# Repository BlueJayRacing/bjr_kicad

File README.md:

# bjr_kicad
jhu blue jay racing daq kicad pcb files

Note: 20xt is mainly for legacy

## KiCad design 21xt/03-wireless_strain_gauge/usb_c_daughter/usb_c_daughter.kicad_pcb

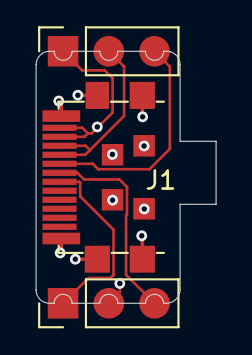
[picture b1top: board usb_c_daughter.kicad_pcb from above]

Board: 4 copper layers, 10.0 x 14.0 mm, 3 parts (0 on the bottom side), 6 nets.

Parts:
J1: USB_C_Plug_USB2.0; USB_C_MOUNT
J3: Conn_01x03; PinHeader_1x03_P2.54mm_Vertical
Je: Conn_01x03; PinSocket_1x03_P2.54mm_Vertical

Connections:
CC: J1.A5 (CC), Je.3
D+: J1.A6 (D+), J3.3
D-: J1.A7 (D-), J3.1
GND: J1.A1 (GND), J1.B12 (GND), Je.1
SHIELD: J1.S1 (SHIELD), J3.2
VBUS: J1.A4 (VBUS), J1.B9 (VBUS), Je.2

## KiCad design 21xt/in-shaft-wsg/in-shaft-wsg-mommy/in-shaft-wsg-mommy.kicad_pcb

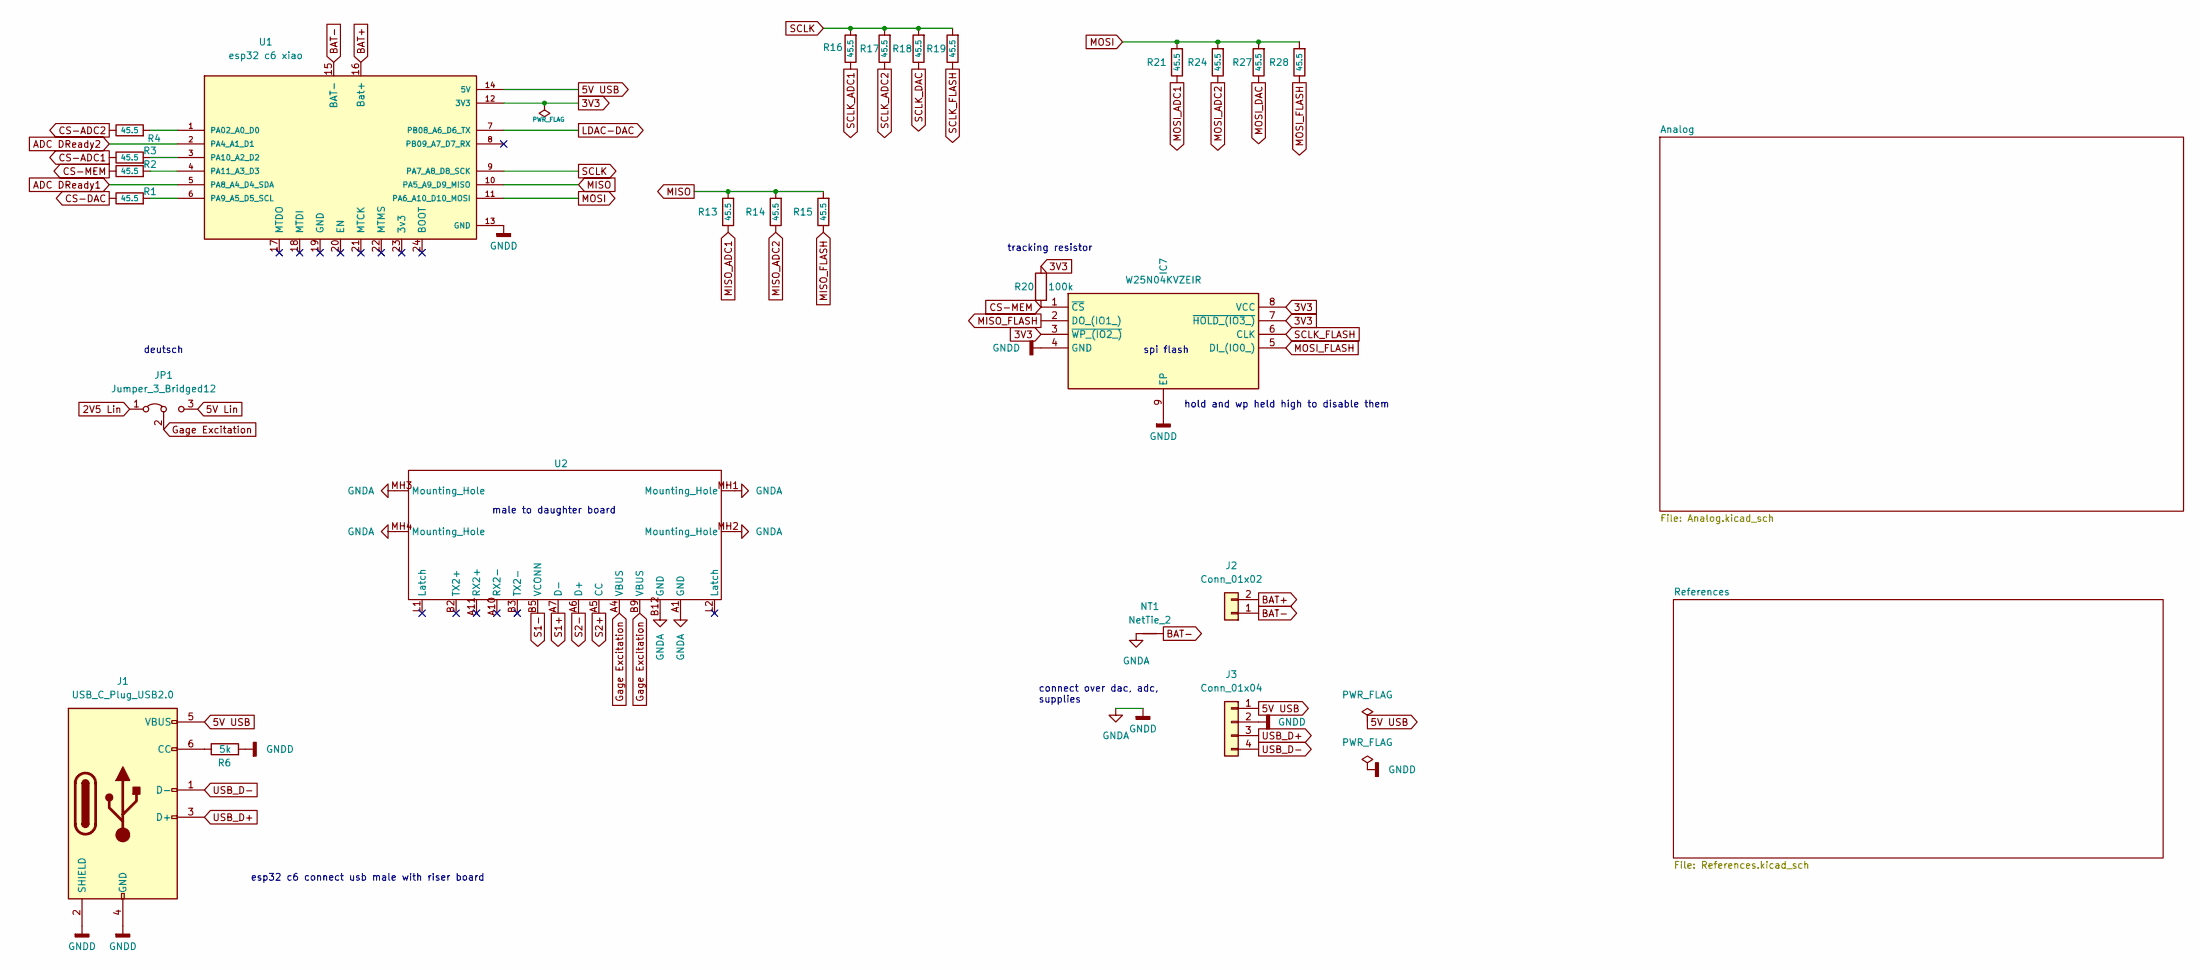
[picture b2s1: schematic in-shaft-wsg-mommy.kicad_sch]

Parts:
IC7: W25N04KVZEIR; SON127P800X600X80-9N-D; Mouser Part Number 454-W25N04KVZEIR
J1: USB_C_Plug_USB2.0; USB_C_PLACE
J2: Conn_01x02; JST_PH_S2B-PH-K_1x02_P2.00mm_Horizontal
J3: Conn_01x04; PinHeader_1x04_P2.00mm_Vertical
JP1: Jumper_3_Bridged12; SolderJumper-3_P2.0mm_Open_TrianglePad1.0x1.5mm
NT1: NetTie_2; NetTie-2_SMD_Pad0.5mm
R1, R2, R3, R4, R13, R14, R15, R16, R17, R18, R19, R21, R24, R27, R28: 45.5; R_0402_1005Metric
R6: 5k; R_0402_1005Metric
R20: 100k; R_0402_1005Metric
U1: esp32 c6 xiao; esp32 c6 smt; PARTREV N/A
U2: USB_C_MOUNT

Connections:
2V5 Lin: JP1.1 (A); also elsewhere on the board
3V3: IC7.3 (~WP_(IO2_)), IC7.7 (~HOLD_(IO3_)), IC7.8 (VCC), R20.1, U1.12 (3V3); also elsewhere on the board
5V Lin: JP1.3 (B); also elsewhere on the board
5V USB: J1.5 (VBUS), J3.1, U1.14 (5V)
ADC DReady1: U1.5 (PA8_A4_D4_SDA); also elsewhere on the board
ADC DReady2: U1.2 (PA4_A1_D1); also elsewhere on the board
BAT+: J2.2, U1.16 (Bat+)
BAT-: J2.1, NT1.2, U1.15 (BAT-)
CS-ADC1: R3.1; also elsewhere on the board
CS-ADC2: R4.1; also elsewhere on the board
CS-DAC: R1.1; also elsewhere on the board
CS-MEM: IC7.1 (~CS), R2.1, R20.2
GNDA: IC7.4 (GND), IC7.9 (EP), J1.2 (SHIELD), J1.4 (GND), J3.2, NT1.1, R6.2, U1.13 (GND), U2.A1 (GND), U2.B12 (GND), U2.MH1 (Mounting_Hole), U2.MH2 (Mounting_Hole), U2.MH3 (Mounting_Hole), U2.MH4 (Mounting_Hole); also elsewhere on the board
Gage Excitation: JP1.2 (C), U2.A4 (VBUS), U2.B9 (VBUS); also elsewhere on the board
LDAC-DAC: U1.7 (PB08_A6_D6_TX); also elsewhere on the board
MISO: R13.2, R14.2, R15.2, U1.10 (PA5_A9_D9_MISO)
MISO_ADC1: R13.1; also elsewhere on the board
MISO_ADC2: R14.1; also elsewhere on the board
MISO_FLASH: IC7.2 (DO_(IO1_)), R15.1
MOSI: R21.2, R24.2, R27.2, R28.2, U1.11 (PA6_A10_D10_MOSI)
MOSI_ADC1: R21.1; also elsewhere on the board
MOSI_ADC2: R24.1; also elsewhere on the board
MOSI_DAC: R27.1; also elsewhere on the board
MOSI_FLASH: IC7.5 (DI_(IO0_)), R28.1
unnamed: J1.6 (CC), R6.1
unnamed: R4.2, U1.1 (PA02_A0_D0)
unnamed: R1.2, U1.6 (PA9_A5_D5_SCL)
unnamed: R3.2, U1.3 (PA10_A2_D2)
unnamed: R2.2, U1.4 (PA11_A3_D3)
S1+: U2.A7 (D-); also elsewhere on the board
S1-: U2.B5 (VCONN); also elsewhere on the board
S2+: U2.A5 (CC); also elsewhere on the board
S2-: U2.A6 (D+); also elsewhere on the board
SCLK: R16.2, R17.2, R18.2, R19.2, U1.9 (PA7_A8_D8_SCK)
SCLK_ADC1: R16.1; also elsewhere on the board
SCLK_ADC2: R17.1; also elsewhere on the board
SCLK_DAC: R18.1; also elsewhere on the board
SCLK_FLASH: IC7.6 (CLK), R19.1
USB_D+: J1.3 (D+), J3.3
USB_D-: J1.1 (D-), J3.4

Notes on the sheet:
connect over dac, adc, supplies
esp32 c6 connect usb male with riser board
spi flash
male to daughter board
deutsch
hold and wp held high to disable them
tracking resistor

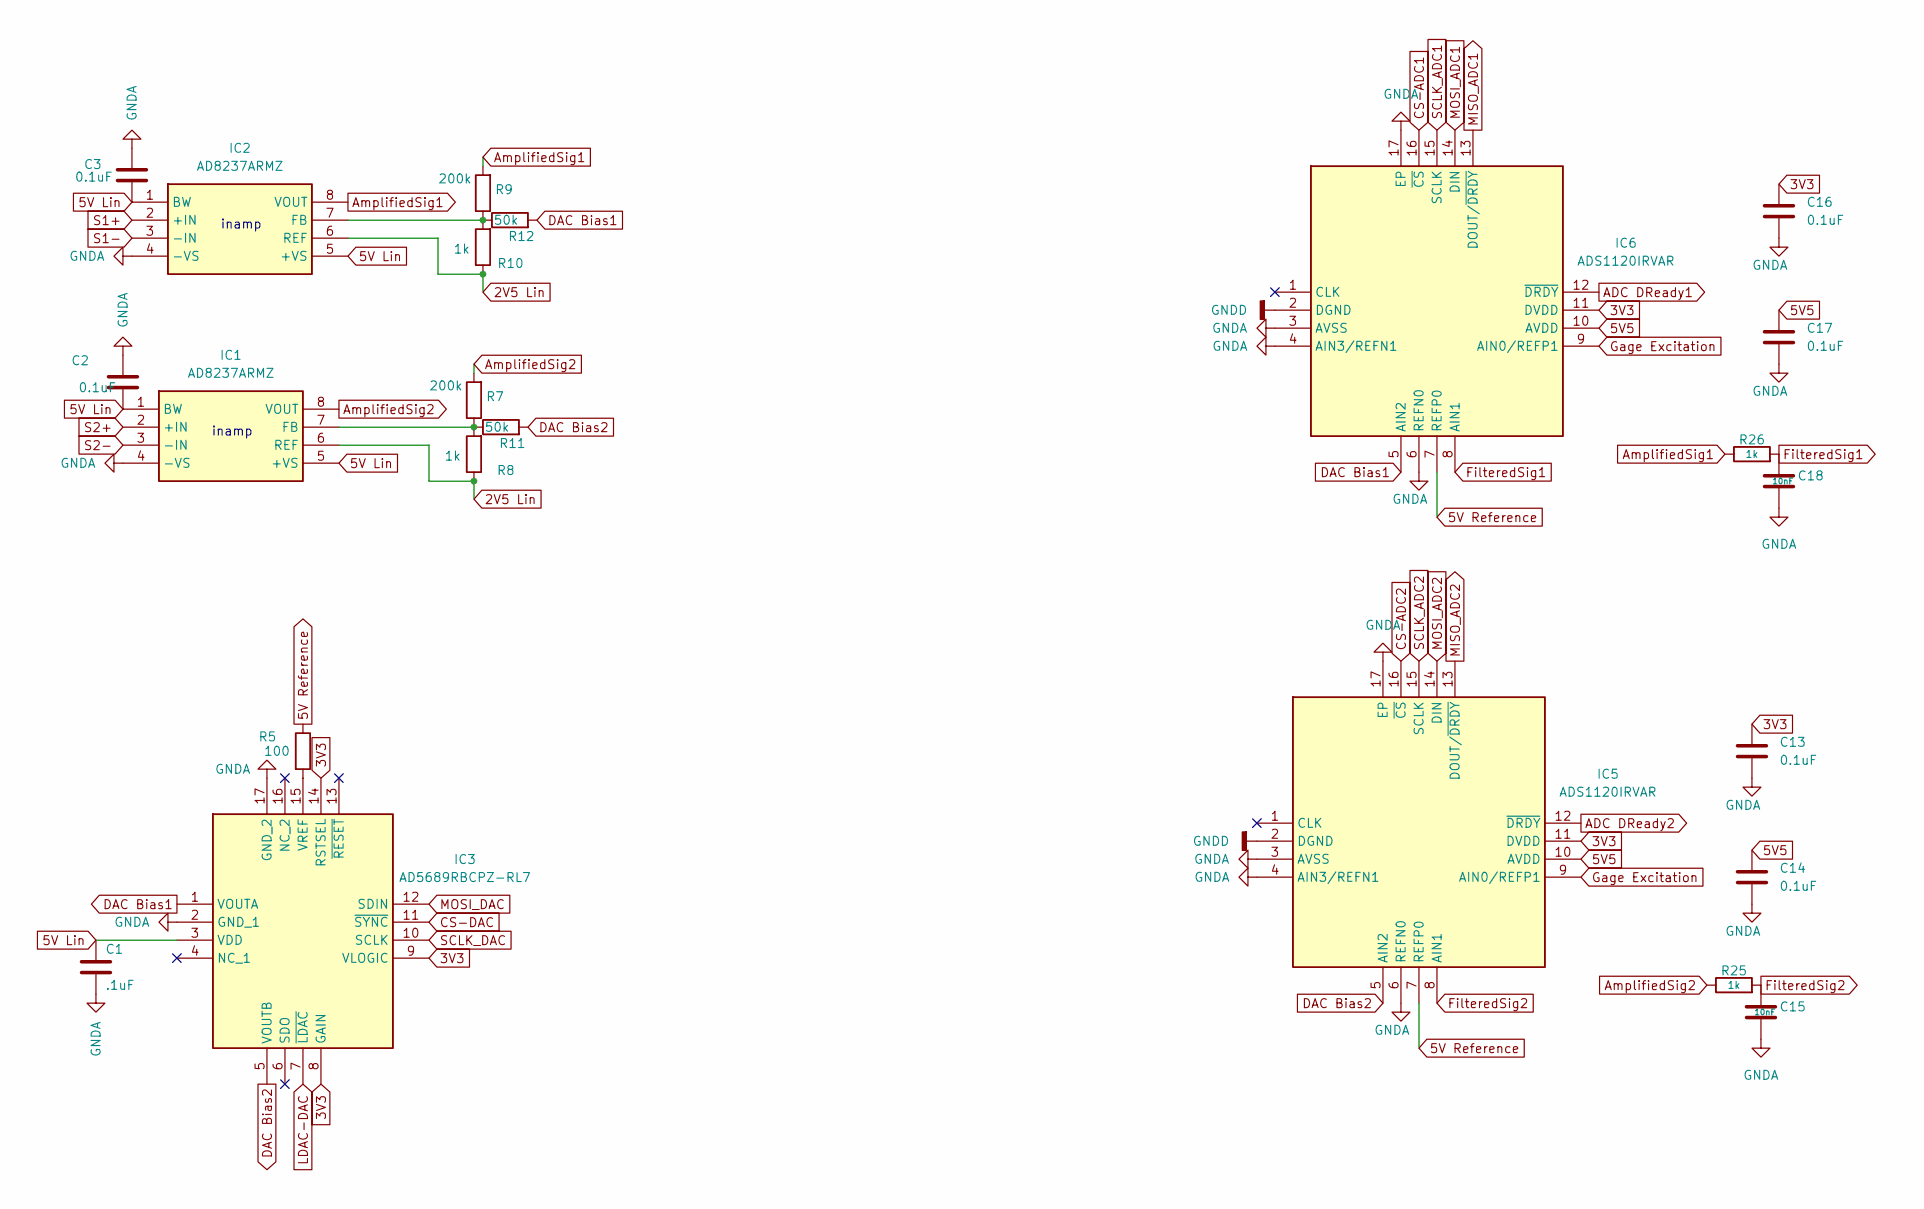
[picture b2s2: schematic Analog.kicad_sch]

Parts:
C1: .1uF; C_0402_1005Metric
C2, C3, C13, C14, C16, C17: 0.1uF; C_0402_1005Metric
C15, C18: 10nF; C_0402_1005Metric
IC1, IC2: AD8237ARMZ; Mouser Part Number 584-AD8237ARMZ
IC3: AD5689RBCPZ-RL7; Mouser Part Number 584-AD5689RBCPZ-R7
IC5, IC6: ADS1120IRVAR; QFN50P350X350X100-17N-D; Mouser Part Number 595-ADS1120IRVAR
R5: 100; R_0402_1005Metric
R7, R9: 200k; R_0402_1005Metric
R8, R10, R25, R26: 1k; R_0402_1005Metric
R11, R12: 50k; R_0402_1005Metric

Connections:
2V5 Lin: IC1.6 (REF), IC2.6 (REF), R8.1, R10.1; also elsewhere on the board
3V3: C13.1, C16.1, IC3.8 (GAIN), IC3.9 (VLOGIC), IC3.14 (RSTSEL), IC5.11 (DVDD), IC6.11 (DVDD); also elsewhere on the board
5V5: C14.1, C17.1, IC5.10 (AVDD), IC6.10 (AVDD); also elsewhere on the board
5V Lin: C1.1, C2.2, C3.2, IC1.1 (BW), IC1.5 (+VS), IC2.1 (BW), IC2.5 (+VS), IC3.3 (VDD); also elsewhere on the board
5V Reference: IC5.7 (REFP0), IC6.7 (REFP0), R5.1; also elsewhere on the board
ADC DReady1: IC6.12 (~DRDY); also elsewhere on the board
ADC DReady2: IC5.12 (~DRDY); also elsewhere on the board
AmplifiedSig1: IC2.8 (VOUT), R9.2, R26.1
AmplifiedSig2: IC1.8 (VOUT), R7.2, R25.1
CS-ADC1: IC6.16 (~CS); also elsewhere on the board
CS-ADC2: IC5.16 (~CS); also elsewhere on the board
CS-DAC: IC3.11 (~SYNC); also elsewhere on the board
DAC Bias1: IC3.1 (VOUTA), IC6.5 (AIN2), R12.2
DAC Bias2: IC3.5 (VOUTB), IC5.5 (AIN2), R11.2
FilteredSig1: C18.1, IC6.8 (AIN1), R26.2
FilteredSig2: C15.1, IC5.8 (AIN1), R25.2
GNDA: C1.2, C2.1, C3.1, C13.2, C14.2, C15.2, C16.2, C17.2, C18.2, IC1.4 (-VS), IC2.4 (-VS), IC3.2 (GND_1), IC3.17 (GND_2), IC5.2 (DGND), IC5.3 (AVSS), IC5.4 (AIN3/REFN1), IC5.6 (REFN0), IC5.17 (EP), IC6.2 (DGND), IC6.3 (AVSS), IC6.4 (AIN3/REFN1), IC6.6 (REFN0), IC6.17 (EP); also elsewhere on the board
Gage Excitation: IC5.9 (AIN0/REFP1), IC6.9 (AIN0/REFP1); also elsewhere on the board
LDAC-DAC: IC3.7 (~LDAC); also elsewhere on the board
MISO_ADC1: IC6.13 (DOUT/~DRDY); also elsewhere on the board
MISO_ADC2: IC5.13 (DOUT/~DRDY); also elsewhere on the board
MOSI_ADC1: IC6.14 (DIN); also elsewhere on the board
MOSI_ADC2: IC5.14 (DIN); also elsewhere on the board
MOSI_DAC: IC3.12 (SDIN); also elsewhere on the board
unnamed: IC1.7 (FB), R7.1, R8.2, R11.1
unnamed: IC2.7 (FB), R9.1, R10.2, R12.1
unnamed: IC3.15 (VREF), R5.2
S1+: IC2.2 (+IN); also elsewhere on the board
S1-: IC2.3 (-IN); also elsewhere on the board
S2+: IC1.2 (+IN); also elsewhere on the board
S2-: IC1.3 (-IN); also elsewhere on the board
SCLK_ADC1: IC6.15 (SCLK); also elsewhere on the board
SCLK_ADC2: IC5.15 (SCLK); also elsewhere on the board
SCLK_DAC: IC3.10 (SCLK); also elsewhere on the board

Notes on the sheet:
inamp

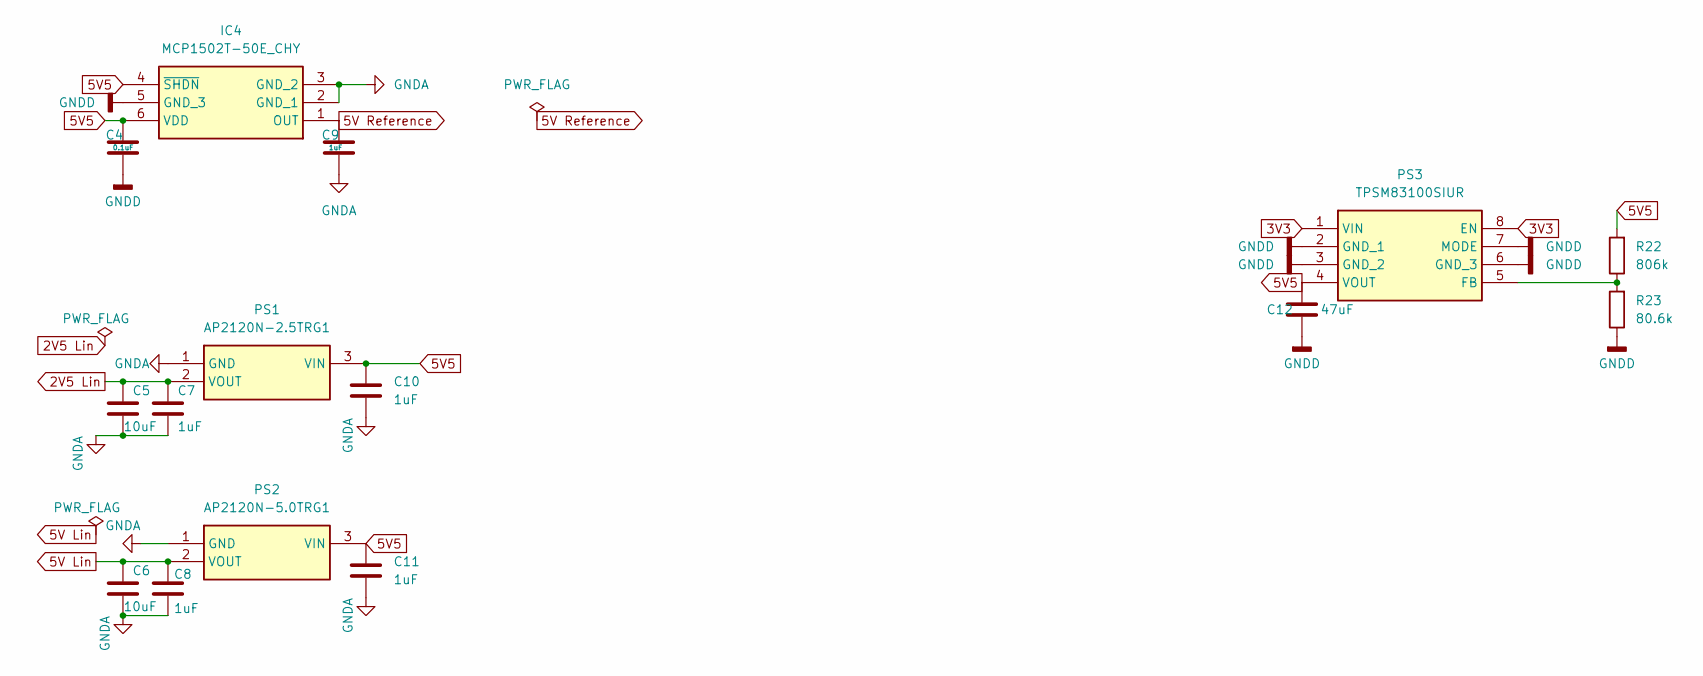
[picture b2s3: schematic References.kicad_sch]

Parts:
C4: 0.1uF; C_0402_1005Metric
C5, C6: 10uF; C_0402_1005Metric
C7, C8, C9, C10, C11: 1uF; C_0402_1005Metric
C12: 47uF; C_0805_2012Metric
IC4: MCP1502T-50E_CHY; SOT95P280X145-6N; Mouser Part Number 579-MCP1501T-50E/CHY
PS1: AP2120N-2.5TRG1; Mouser Part Number 621-AP2120N-5.0TRG1
PS2: AP2120N-5.0TRG1; Mouser Part Number 621-AP2120N-5.0TRG1
PS3: TPSM83100SIUR; Mouser Part Number 595-TPSM83100SIUR
R22: 806k; R_0402_1005Metric
R23: 80.6k; R_0402_1005Metric

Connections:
2V5 Lin: C5.1, C7.1, PS1.2 (VOUT); also elsewhere on the board
3V3: PS3.1 (VIN), PS3.8 (EN); also elsewhere on the board
5V5: C4.1, C10.1, C11.1, C12.1, IC4.4 (~SHDN), IC4.6 (VDD), PS1.3 (VIN), PS2.3 (VIN), PS3.4 (VOUT), R22.2; also elsewhere on the board
5V Lin: C6.1, C8.1, PS2.2 (VOUT); also elsewhere on the board
5V Reference: C9.1, IC4.1 (OUT); also elsewhere on the board
GNDA: C4.2, C5.2, C6.2, C7.2, C8.2, C9.2, C10.2, C11.2, C12.2, IC4.2 (GND_1), IC4.3 (GND_2), IC4.5 (GND_3), PS1.1 (GND), PS2.1 (GND), PS3.2 (GND_1), PS3.3 (GND_2), PS3.6 (GND_3), PS3.7 (MODE), R23.1; also elsewhere on the board
unnamed: PS3.5 (FB), R22.1, R23.2

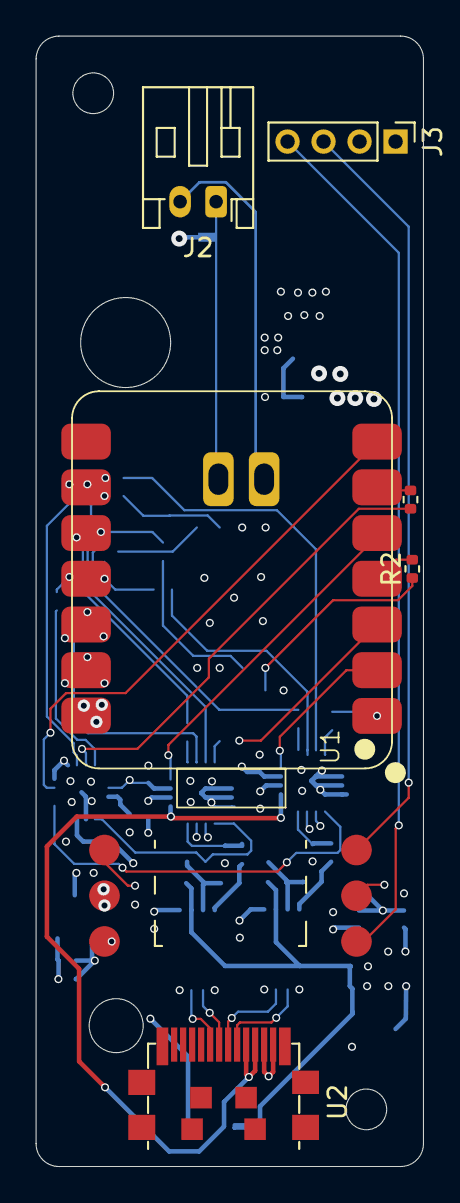
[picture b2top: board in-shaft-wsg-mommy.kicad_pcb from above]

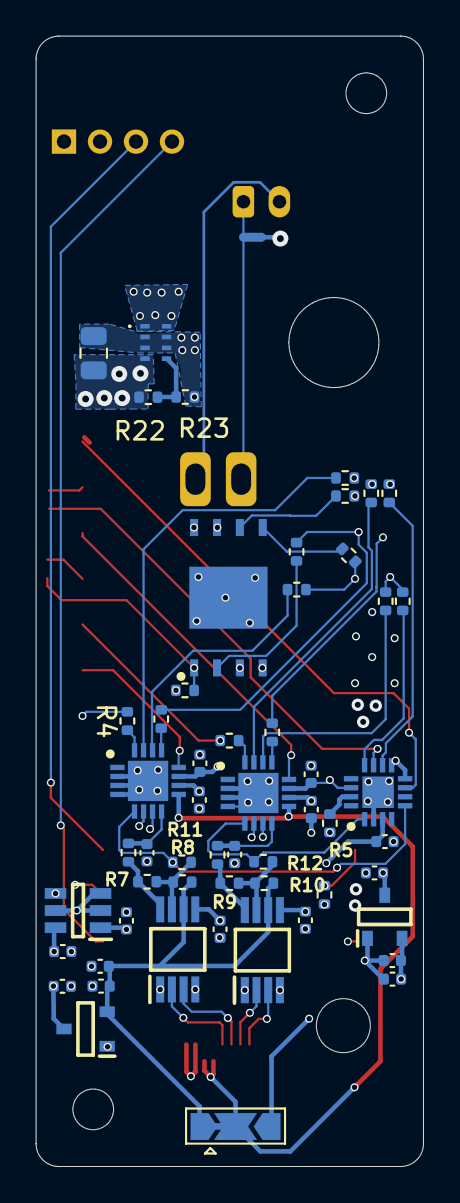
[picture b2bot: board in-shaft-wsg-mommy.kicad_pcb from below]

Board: 4 copper layers, 21.5 x 62.8 mm, 63 parts (56 on the bottom side), 52 nets.

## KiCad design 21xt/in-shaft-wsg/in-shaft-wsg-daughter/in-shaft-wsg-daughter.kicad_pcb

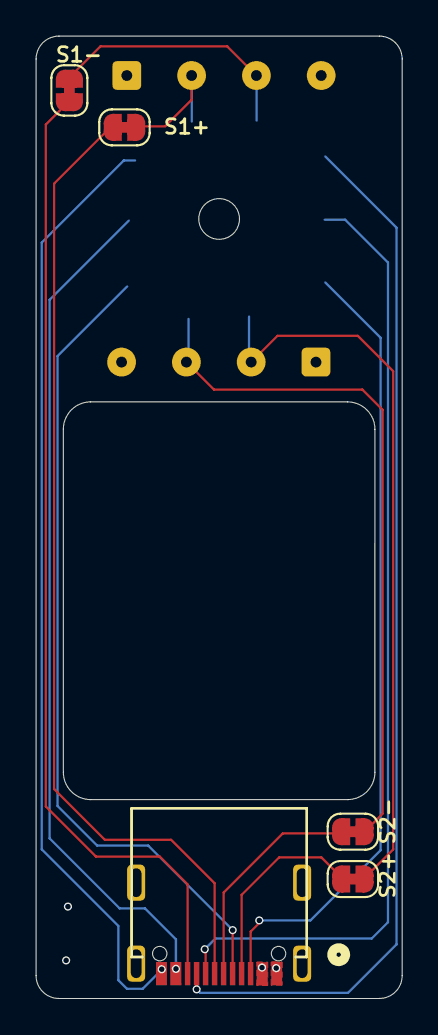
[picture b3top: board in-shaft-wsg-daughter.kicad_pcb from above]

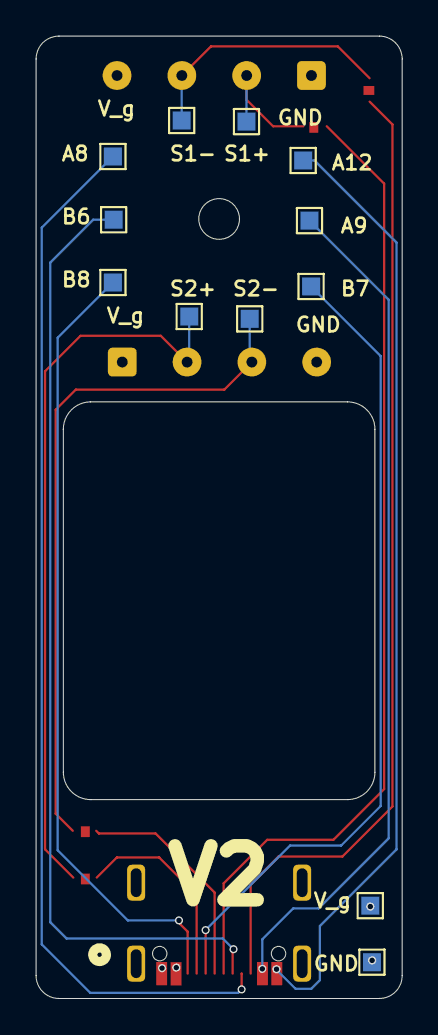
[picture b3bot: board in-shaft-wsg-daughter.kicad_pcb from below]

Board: 4 copper layers, 20.3 x 53.5 mm, 19 parts (12 on the bottom side), 16 nets.

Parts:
J1: tall_usb_female; tall usb female
J2, J3: Conn_01x04; SolderWire-0.1sqmm_1x04_P3.6mm_D0.4mm_OD1mm
JP1, JP2, JP3, JP4: SolderJumper_2_Bridged; SolderJumper-2_P1.3mm_Bridged_RoundedPad1.0x1.5mm
TP1, TP2, TP3, TP4, TP5, TP6, TP7, TP8, TP9, TP10, TP11, TP12: TestPoint; TestPoint_Pad_1.0x1.0mm

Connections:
GNDA: J1.A1, J1.B12, J1.GND, J2.4, J3.4, TP1.1
Gage Excitation: J1.A4, J1.B9, J2.1, J3.1, TP2.1
unnamed: J1.A8, TP10.1
unnamed: J1.A9, J1.B4, TP11.1
unnamed: J1.A12, J1.B1, TP12.1
unnamed: J1.B6, TP9.1
unnamed: J1.B7, TP8.1
unnamed: J1.B8, TP7.1
unnamed: J1.A7, JP1.1 (A)
unnamed: J1.B5, JP2.1 (A)
unnamed: J1.A5, JP3.1 (A)
unnamed: J1.A6, JP4.1 (A)
S1+: J2.2, JP1.2 (B), TP4.1
S1-: J2.3, JP2.2 (B), TP3.1
S2+: J3.2, JP3.2 (B), TP6.1
S2-: J3.3, JP4.2 (B), TP5.1

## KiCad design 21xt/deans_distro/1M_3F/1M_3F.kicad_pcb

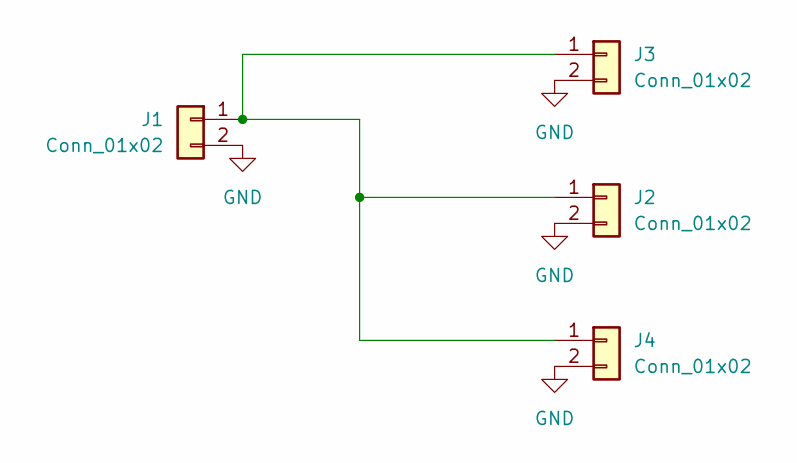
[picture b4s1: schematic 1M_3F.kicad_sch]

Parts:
J1: Conn_01x02; Deans Connector Male
J2, J3, J4: Conn_01x02; Deans Connector Female

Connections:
GND: J1.2, J2.2, J3.2, J4.2
unnamed: J1.1, J2.1, J3.1, J4.1

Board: 4 copper layers, 4 parts (3 on the bottom side), 2 nets, no tracks yet.

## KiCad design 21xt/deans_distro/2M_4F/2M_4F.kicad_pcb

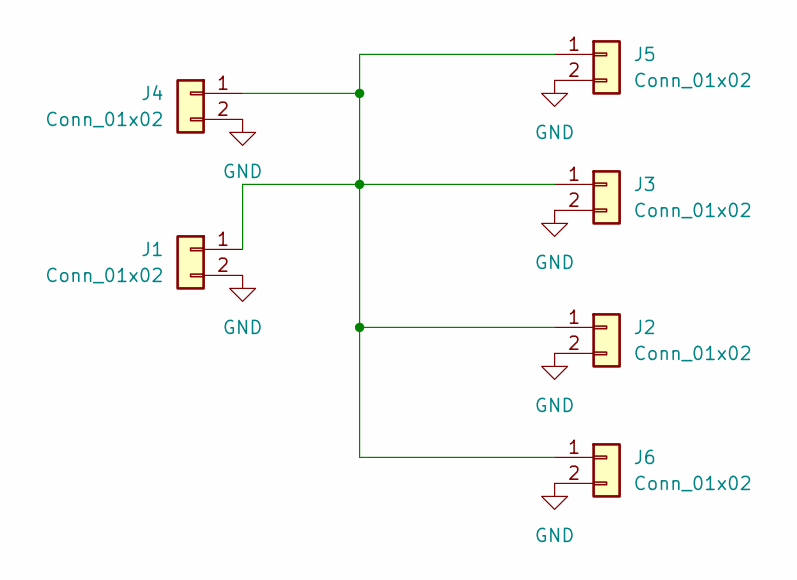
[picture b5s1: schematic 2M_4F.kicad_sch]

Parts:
J1, J4: Conn_01x02; Deans Connector Male
J2, J3, J5, J6: Conn_01x02; Deans Connector Female

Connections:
GND: J1.2, J2.2, J3.2, J4.2, J5.2, J6.2
unnamed: J1.1, J2.1, J3.1, J4.1, J5.1, J6.1

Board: 6 copper layers, 6 parts (4 on the bottom side), 2 nets, no tracks yet.

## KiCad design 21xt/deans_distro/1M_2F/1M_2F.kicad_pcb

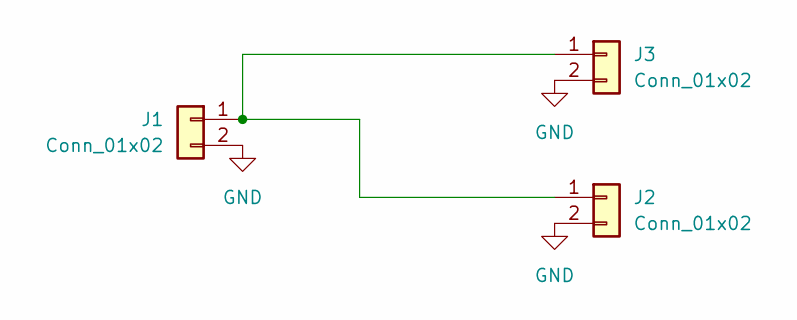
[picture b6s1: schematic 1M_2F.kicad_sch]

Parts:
J1: Conn_01x02; Deans Connector Male
J2, J3: Conn_01x02; Deans Connector Female

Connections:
GND: J1.2, J2.2, J3.2
unnamed: J1.1, J2.1, J3.1

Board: 6 copper layers, 3 parts (2 on the bottom side), 2 nets, no tracks yet.

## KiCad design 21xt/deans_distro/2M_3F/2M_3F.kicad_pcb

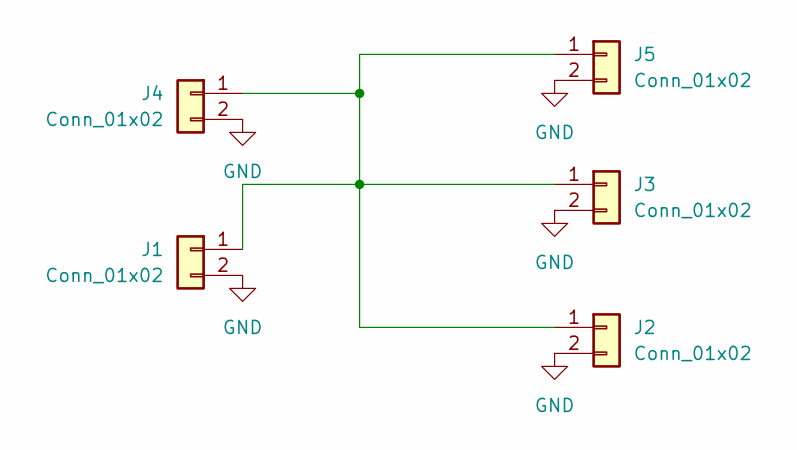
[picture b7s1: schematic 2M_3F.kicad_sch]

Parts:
J1, J4: Conn_01x02; Deans Connector Male
J2, J3, J5: Conn_01x02; Deans Connector Female

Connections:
GND: J1.2, J2.2, J3.2, J4.2, J5.2
unnamed: J1.1, J2.1, J3.1, J4.1, J5.1

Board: 6 copper layers, 5 parts (3 on the bottom side), 2 nets, no tracks yet.

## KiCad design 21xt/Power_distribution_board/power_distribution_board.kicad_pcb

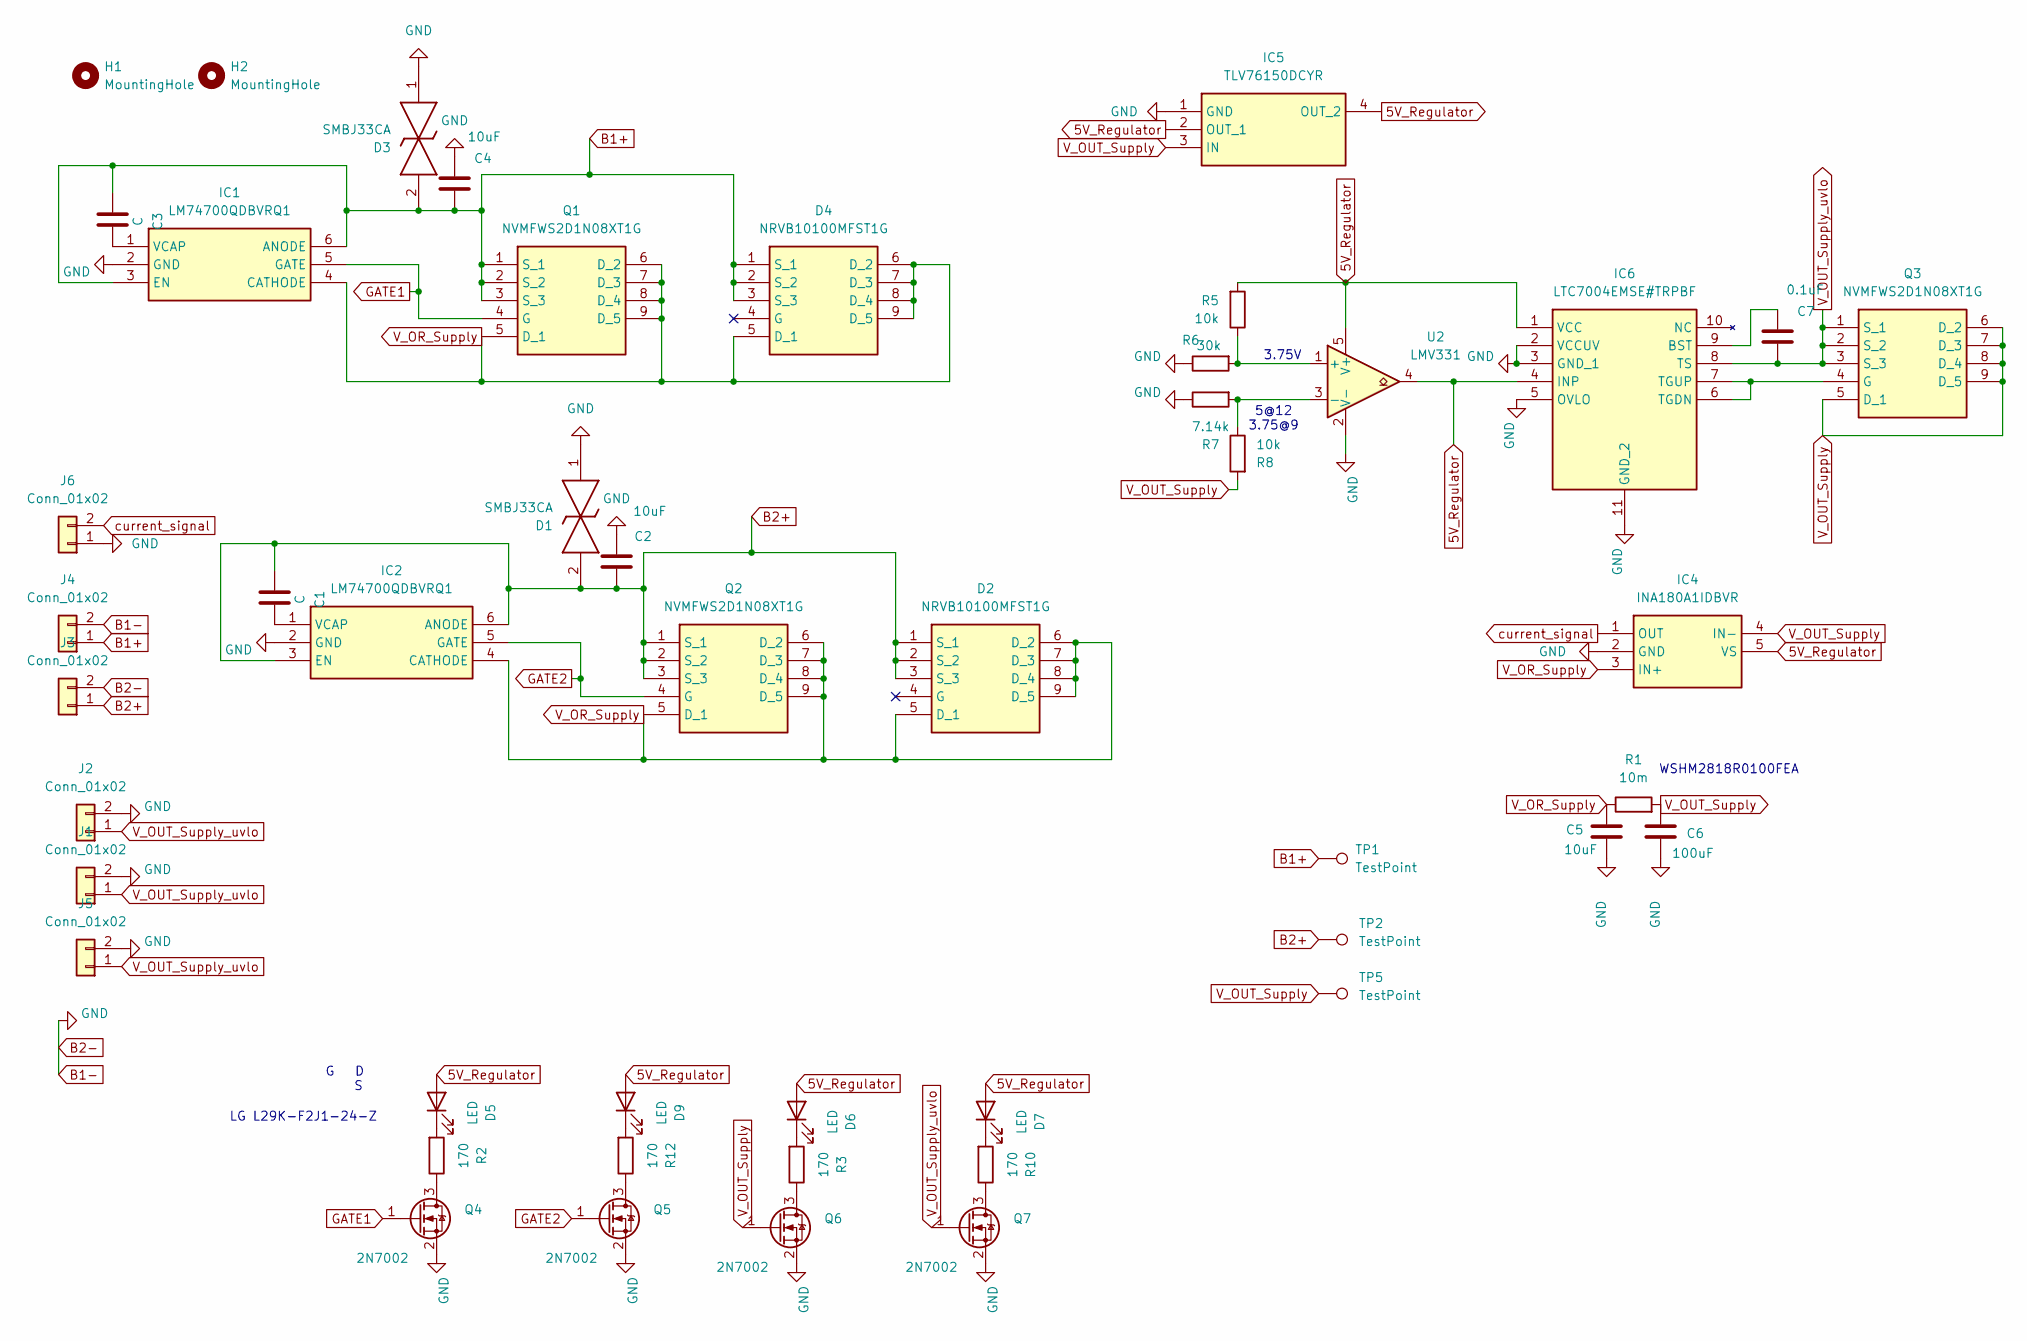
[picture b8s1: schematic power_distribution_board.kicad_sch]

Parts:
C1, C3: C; C_0402_1005Metric
C2, C4, C5: 10uF; C_0402_1005Metric
C6: 100uF; C_0603_1608Metric
C7: 0.1uF; C_0402_1005Metric
D1, D3: SMBJ33CA; Mouser Part Number 652-SMBJ33CA
D2, D4: NRVB10100MFST1G; NRVTS10100EMFST1G; Mouser Part Number 863-NRVB10100MFST1G
D5, D6, D7, D9: LED; LED_0603_1608Metric
H1, H2: MountingHole; MountingHole_3.2mm_M3
IC1, IC2: LM74700QDBVRQ1; Mouser Part Number 595-LM74700QDBVRQ1
IC4: INA180A1IDBVR; Mouser Part Number 595-INA180A1IDBVR
IC5: TLV76150DCYR; Mouser Part Number 595-TLV76150DCYR
IC6: LTC7004EMSE#TRPBF; SOP50P490X110-11N; Mouser Part Number 584-7004EMSETRPBF
J1, J2, J5: Conn_01x02; Deans Connector Female
J3, J4: Conn_01x02; Deans Connector Male
J6: Conn_01x02; JST_EH_S2B-EH_1x02_P2.50mm_Horizontal
Q1, Q2, Q3: NVMFWS2D1N08XT1G; NTMFWS1D5N08XT1G; Mouser Part Number 863-NVMFWS2D1N08XT1G
Q4, Q5, Q6, Q7: 2N7002; SOT-23
R1: 10m; RESC_WSHM2818R0150FEA
R2, R3, R10, R12: 170; R_0402_1005Metric
R5, R8: 10k; R_0402_1005Metric
R6: 30k; R_0402_1005Metric
R7: 7.14k; R_0402_1005Metric
TP1, TP2, TP5: TestPoint; TestPoint_Pad_1.0x1.0mm
U2: LMV331; SOT-23-5

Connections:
5V_Regulator: D5.2 (A), D6.2 (A), D7.2 (A), D9.2 (A), IC4.5 (VS), IC5.2 (OUT_1), IC5.4 (OUT_2), IC6.1 (VCC), IC6.4 (INP), R5.2, U2.4, U2.5 (V+)
B1+: C3.1, C4.2, D3.2, D4.1 (S_1), D4.2 (S_2), D4.3 (S_3), IC1.3 (EN), IC1.6 (ANODE), J4.1, Q1.1 (S_1), Q1.2 (S_2), Q1.3 (S_3), TP1.1
B1-: C2.1, C4.1, C5.2, C6.2, D1.1, D3.1, IC1.2 (GND), IC2.2 (GND), IC4.2 (GND), IC5.1 (GND), IC6.2 (VCCUV), IC6.3 (GND_1), IC6.5 (OVLO), IC6.11 (GND_2), J1.2, J2.2, J3.2, J4.2, J5.2, J6.1, Q4.2 (S), Q5.2 (S), Q6.2 (S), Q7.2 (S), R6.1, R7.1, U2.2 (V-)
B2+: C1.1, C2.2, D1.2, D2.1 (S_1), D2.2 (S_2), D2.3 (S_3), IC2.3 (EN), IC2.6 (ANODE), J3.1, Q2.1 (S_1), Q2.2 (S_2), Q2.3 (S_3), TP2.1
GATE1: IC1.5 (GATE), Q1.4 (G), Q4.1 (G)
GATE2: IC2.5 (GATE), Q2.4 (G), Q5.1 (G)
unnamed: D5.1 (K), R2.2
unnamed: D6.1 (K), R3.2
unnamed: D7.1 (K), R10.2
unnamed: D9.1 (K), R12.2
unnamed: C3.2, IC1.1 (VCAP)
unnamed: C1.2, IC2.1 (VCAP)
unnamed: C7.1, IC6.9 (BST)
unnamed: IC6.6 (TGDN), IC6.7 (TGUP), Q3.4 (G)
unnamed: Q4.3 (D), R2.1
unnamed: Q5.3 (D), R12.1
unnamed: Q6.3 (D), R3.1
unnamed: Q7.3 (D), R10.1
unnamed: R5.1, R6.2, U2.1 (+)
unnamed: R7.2, R8.1, U2.3 (-)
V_OR_Supply: C5.1, D2.5 (D_1), D2.6 (D_2), D2.7 (D_3), D2.8 (D_4), D2.9 (D_5), D4.5 (D_1), D4.6 (D_2), D4.7 (D_3), D4.8 (D_4), D4.9 (D_5), IC1.4 (CATHODE), IC2.4 (CATHODE), IC4.3 (IN+), Q1.5 (D_1), Q1.6 (D_2), Q1.7 (D_3), Q1.8 (D_4), Q1.9 (D_5), Q2.5 (D_1), Q2.6 (D_2), Q2.7 (D_3), Q2.8 (D_4), Q2.9 (D_5), R1.1
V_OUT_Supply: C6.1, IC4.4 (IN-), IC5.3 (IN), Q3.5 (D_1), Q3.6 (D_2), Q3.7 (D_3), Q3.8 (D_4), Q3.9 (D_5), Q6.1 (G), R1.2, R8.2, TP5.1
V_OUT_Supply_uvlo: C7.2, IC6.8 (TS), J1.1, J2.1, J5.1, Q3.1 (S_1), Q3.2 (S_2), Q3.3 (S_3), Q7.1 (G)
current_signal: IC4.1 (OUT), J6.2

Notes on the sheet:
5@12 3.75@9
3.75V
WSHM2818R0100FEA
G D S
LG L29K-F2J1-24-Z

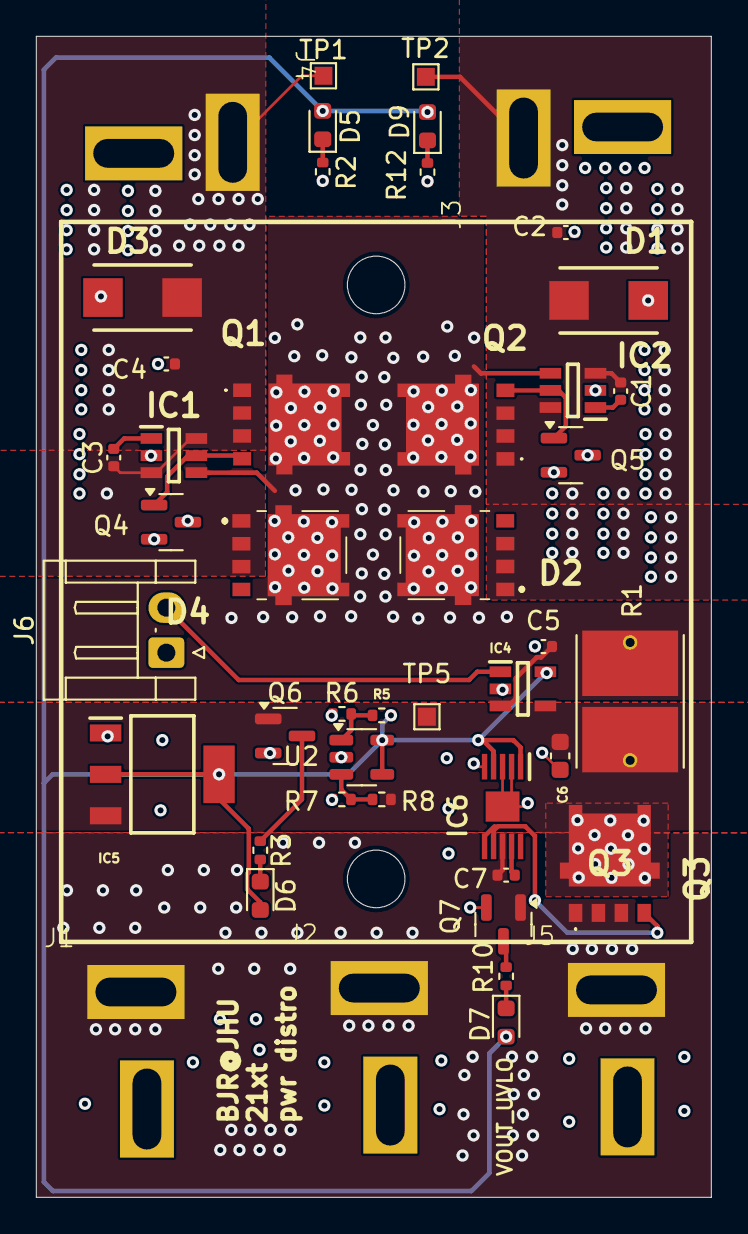
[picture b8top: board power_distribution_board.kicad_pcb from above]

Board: 4 copper layers, 37.5 x 64.5 mm, 48 parts (0 on the bottom side), 24 nets.
